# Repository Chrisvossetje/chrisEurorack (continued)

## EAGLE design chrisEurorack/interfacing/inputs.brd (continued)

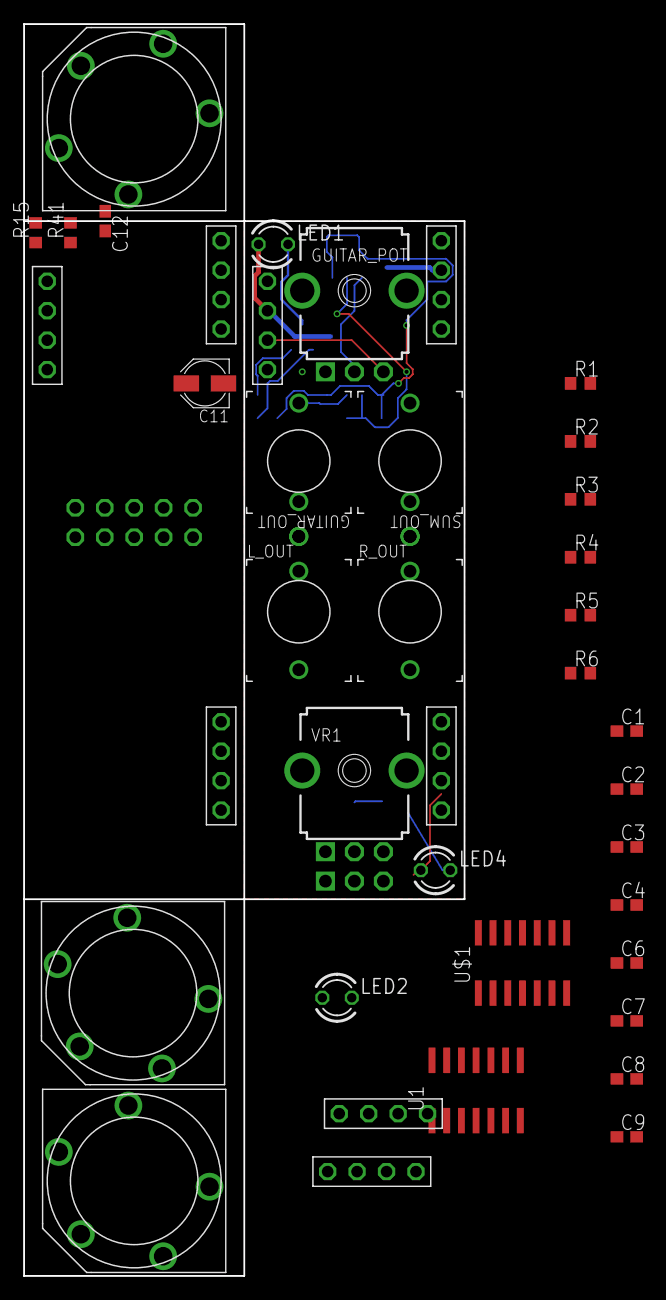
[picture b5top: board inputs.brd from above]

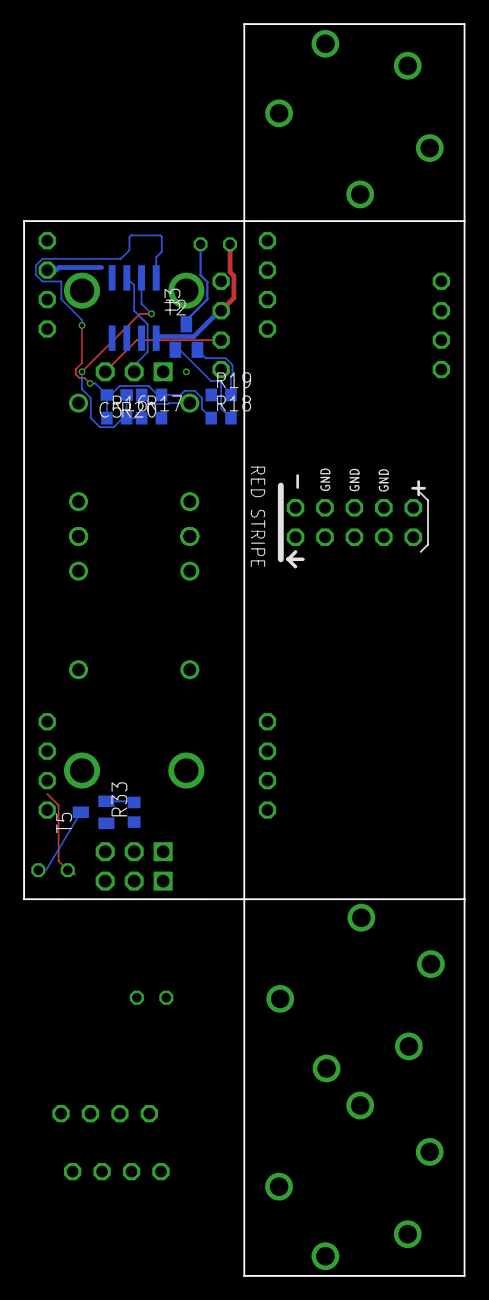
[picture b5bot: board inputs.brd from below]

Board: 2 copper layers, 38.0 x 108.0 mm, 51 parts (11 on the bottom side), 30 nets.

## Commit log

2018-05-22 Goeie
2018-05-22 Cleanup
    Deletee
2018-05-22 Fix!
